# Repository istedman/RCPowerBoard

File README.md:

# RCPowerBoard

A power distribution and battery monitor PCB for radio control vehicles. It can handle up to 15A, I use it on my smaller boats without issue.
Power connections are via plated through-hole or deans/T connectors. There are 4 pairs of smaller holes, connected via a 3.15A polyfuse, for accessory circuits. This protects the battery from short circuits in the accessory devices.

A PIC12F1840 microcontroller monitors the battery/cell voltages and when it gets too low, a buzzer will sound to let you know.

## Supported battery types

4-8 cell NiMh
1-3 cell Lipo
6V or 12V lead acid.

## Software
The design is minimal. A jumper identifies the battery type to monitor, providing you set this with a freshly charged battery pack, it will correctly determine the cell count and store the required settings in EEPROM. Only needs to be done once.
The BatteryMonitor.X directory contains the full source code, exported from MPLabX 6.20

**The software is designed to monitor the battery pack to these lower levels:**
_Lithium Polymer (LiPo)_
Single cell (1S) Lipo    3.6V
Duall cell (2S) Lipo     7.2V
Triple cell (3S) Lipo    10.8V
#define TRIPLE_LIPO_HIGH    12.600     // 12.6V

_Lead acid/AGM cell voltages_
 100% 2.12-2.15V per cell
 20% 1.93V/cell
 0% 1.75V/cell
 We will warn at 20% or 1.93V/cell
6V lower limit is  5.790V
12V lower limit is 11.580V     

_NiMH battery packs_
4 Cell NiMh    4.000V
5 Cell NiMh    5.000V    
6 Cell NiMh    6.00V
7 Cell NiMh    7.00V
8 Cell NiMh    8.00V

The software uses the internal A/D converter of the PIC microcontroller to sample the cell voltage, average it and if it drops below the limits detailed above, it will sound the buzzer. The A/D sampling is at a low rate, this was found to be effective in filtering out momentary supply blips when they accured, eliminating false failures.

Microchip Code Configurator (MCC) was used to setup the device and calibrate the internal voltage reference.

**Measured accuracy has been +/- 0.8% at room temperature** the 1% resistors used in the potential divider, contribute to the error in measurement, which was around 80mV in a 14V range.

## Known issues

The MCP2030 programming header is wrong, I had to swap signals around, will fix it in the next PCB iteration.
The deans/T connector footprint is off, again will be fixed in next revision.
The software only supports Nimh cells with even number of cells.
The PCB is bigger than it needs to be. I have 25 PCBs so there is no rush to fix the design, yet.

## Future development
A new, smaller design is in development that just monitors the battery and supports a wider range of chemistries/types. It can operate from a single cell Lipo or 3 NiMh cells. Plan to publish this later in the year, when finished.

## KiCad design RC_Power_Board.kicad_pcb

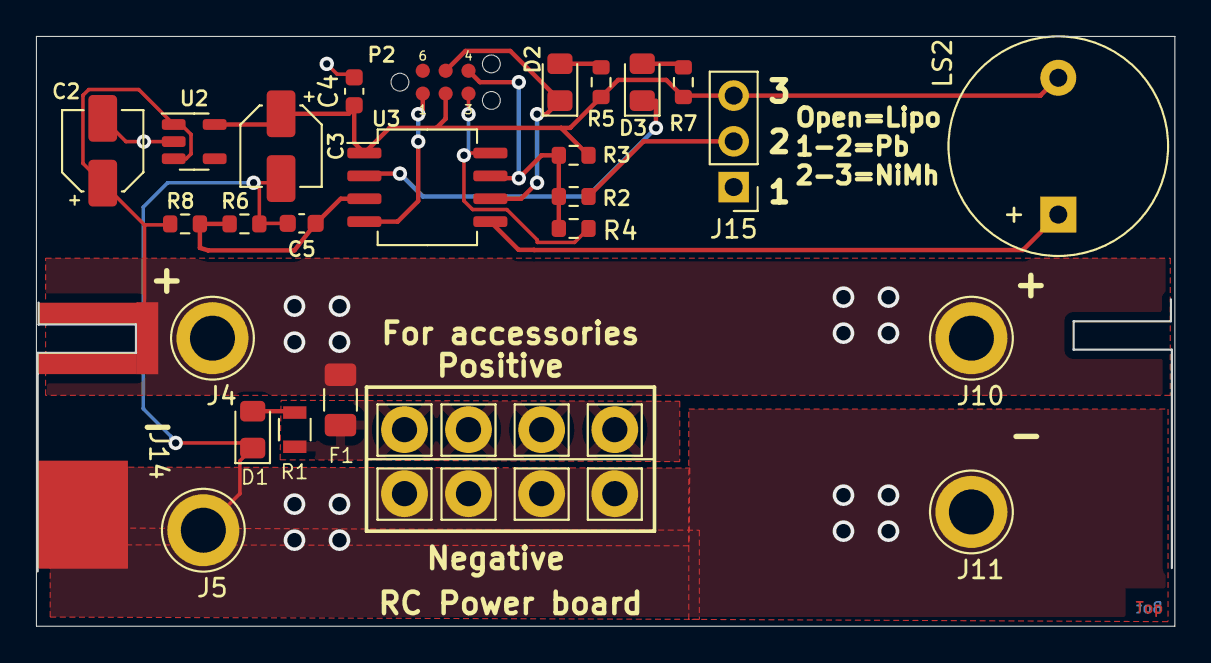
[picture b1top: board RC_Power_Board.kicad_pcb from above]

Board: 2 copper layers, 63.2 x 32.7 mm, 35 parts (1 on the bottom side), 14 nets.

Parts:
C2: 1uF; CP_Elec_4x5.4
C3: 4.7uF; CP_Elec_4x5.4
C4: 100n; C_0603_1608Metric
C5: 100p; C_0603_1608Metric
D1, D2, D3: LED; LED_0805_2012Metric_Pad1.15x1.40mm_HandSolder
F1: 3.15A; Fuse_1206_3216Metric
J1, J14: BATTERY_CONN_DEANS; Deans_PCB
J2, J3, J6, J7, J8, J9, J12, J13: CONN_01POGOPIN_HOLE_LARGE; Pin_D1.4mm_L8.5mm_W2.8mm_FlatFork
J4, J5, J10, J11: CONN_01POGOPIN_HOLE_LARGE; TestPoint_Loop_D3.80mm_Drill2.5mm
J15: CONN_03; PinHeader_1x03_P2.54mm_Vertical
LS2: BUZZER-PTH; Buzzer_12x9.5RM7.6
P2: TC2030-MCP; TC2030-IDC-NL
R1: 2k2; R_0805
R2: 1K; R_0603_1608Metric
R3, R4, R6: 10K; R_0603_1608Metric
R5, R7: 2k2; R_0603_1608Metric
R8: 22K; R_0603_1608Metric
U2: MIC5205-5.0YM5; SOT-23-5
U3: PIC12F683-ISN; SO-8_5.3x6.2mm_P1.27mm

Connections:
/MICRO_+5V: C3.1, C4.1, J15.3, LS2.2 (-), P2.2 (Vdd), R3.2, R5.1, R7.1, U2.5 (OUT), U3.1 (VDD)
/VBAT+: C2.1, F1.2, J1.+, J4.1, J10.1, J14.+, R8.2, U2.1 (IN), U2.3 (EN)
/VBAT-: C2.2, C3.2, C4.2, C5.2, D1.1 (K), J1.-, J5.1, J6.1, J7.1, J11.1, J12.1, J13.1, J14.-, J15.1, P2.3 (GND), R4.1, R6.1, U2.2 (GND), U3.8 (VSS)
/VBAT_FUSED: F1.1, J2.1, J3.1, J8.1, J9.1, R1.1
/Vbat_mon: C5.1, R6.2, R8.1, U3.3 (GP4)
unnamed: D1.2 (A), R1.2
unnamed: D2.1 (K), P2.5 (PGC), U3.6 (GP1)
unnamed: D2.2 (A), R5.2
unnamed: D3.1 (K), U3.2 (GP5)
unnamed: D3.2 (A), R7.2
unnamed: J15.2, R2.2
unnamed: LS2.1 (+), U3.5 (GP2)
unnamed: P2.1 (MCLR/Vpp), U3.4 (GP3)
unnamed: P2.4 (PGD), R2.1, R3.1, R4.2, U3.7 (GP0)

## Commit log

2025-05-29 Initial software commit.
2025-06-25 Add files via upload
    Uploaded software source files, outside of a Zip file, for easier perusal.
